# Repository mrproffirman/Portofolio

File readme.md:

**Projects that has been included are an already completed one and has been approved by all related party to be documented in this manner**

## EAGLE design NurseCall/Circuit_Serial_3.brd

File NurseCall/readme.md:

# Sistem Graphical User Interface untuk NurseCall Analog 

**Overview**<br />
Alat digunakan untuk membaca masukan dari sistem nursecall analog yang sudah ada. Pembacaan digunakan untuk menampilkan nomor kamar pada monitor dan melakukan panggilan pada audio. Secara hardware, sistem terdiri dari <br />
[NurseCall -> Hardware Interface -> SBC -> Monitor].

**Fitur Alat**
1. Membaca sinyal dari sistem NurseCall 0-24V sebanyak 36 Input biasa + 11 Emergency secara parallel
2. Isolasi sinyal input dari sistem utama 5V
3. Mengkonversi bacaan menjadi data digital yang dapat dibaca Single Board Computer.

*Sketsa Hubungan antara sistem monitor yang dibuat dengan NurseCall*

*Sirkuit Hardware Interface menggunakan Arduino Nano*

*GUI yang Dihasilkan*

*Hardware Interface*

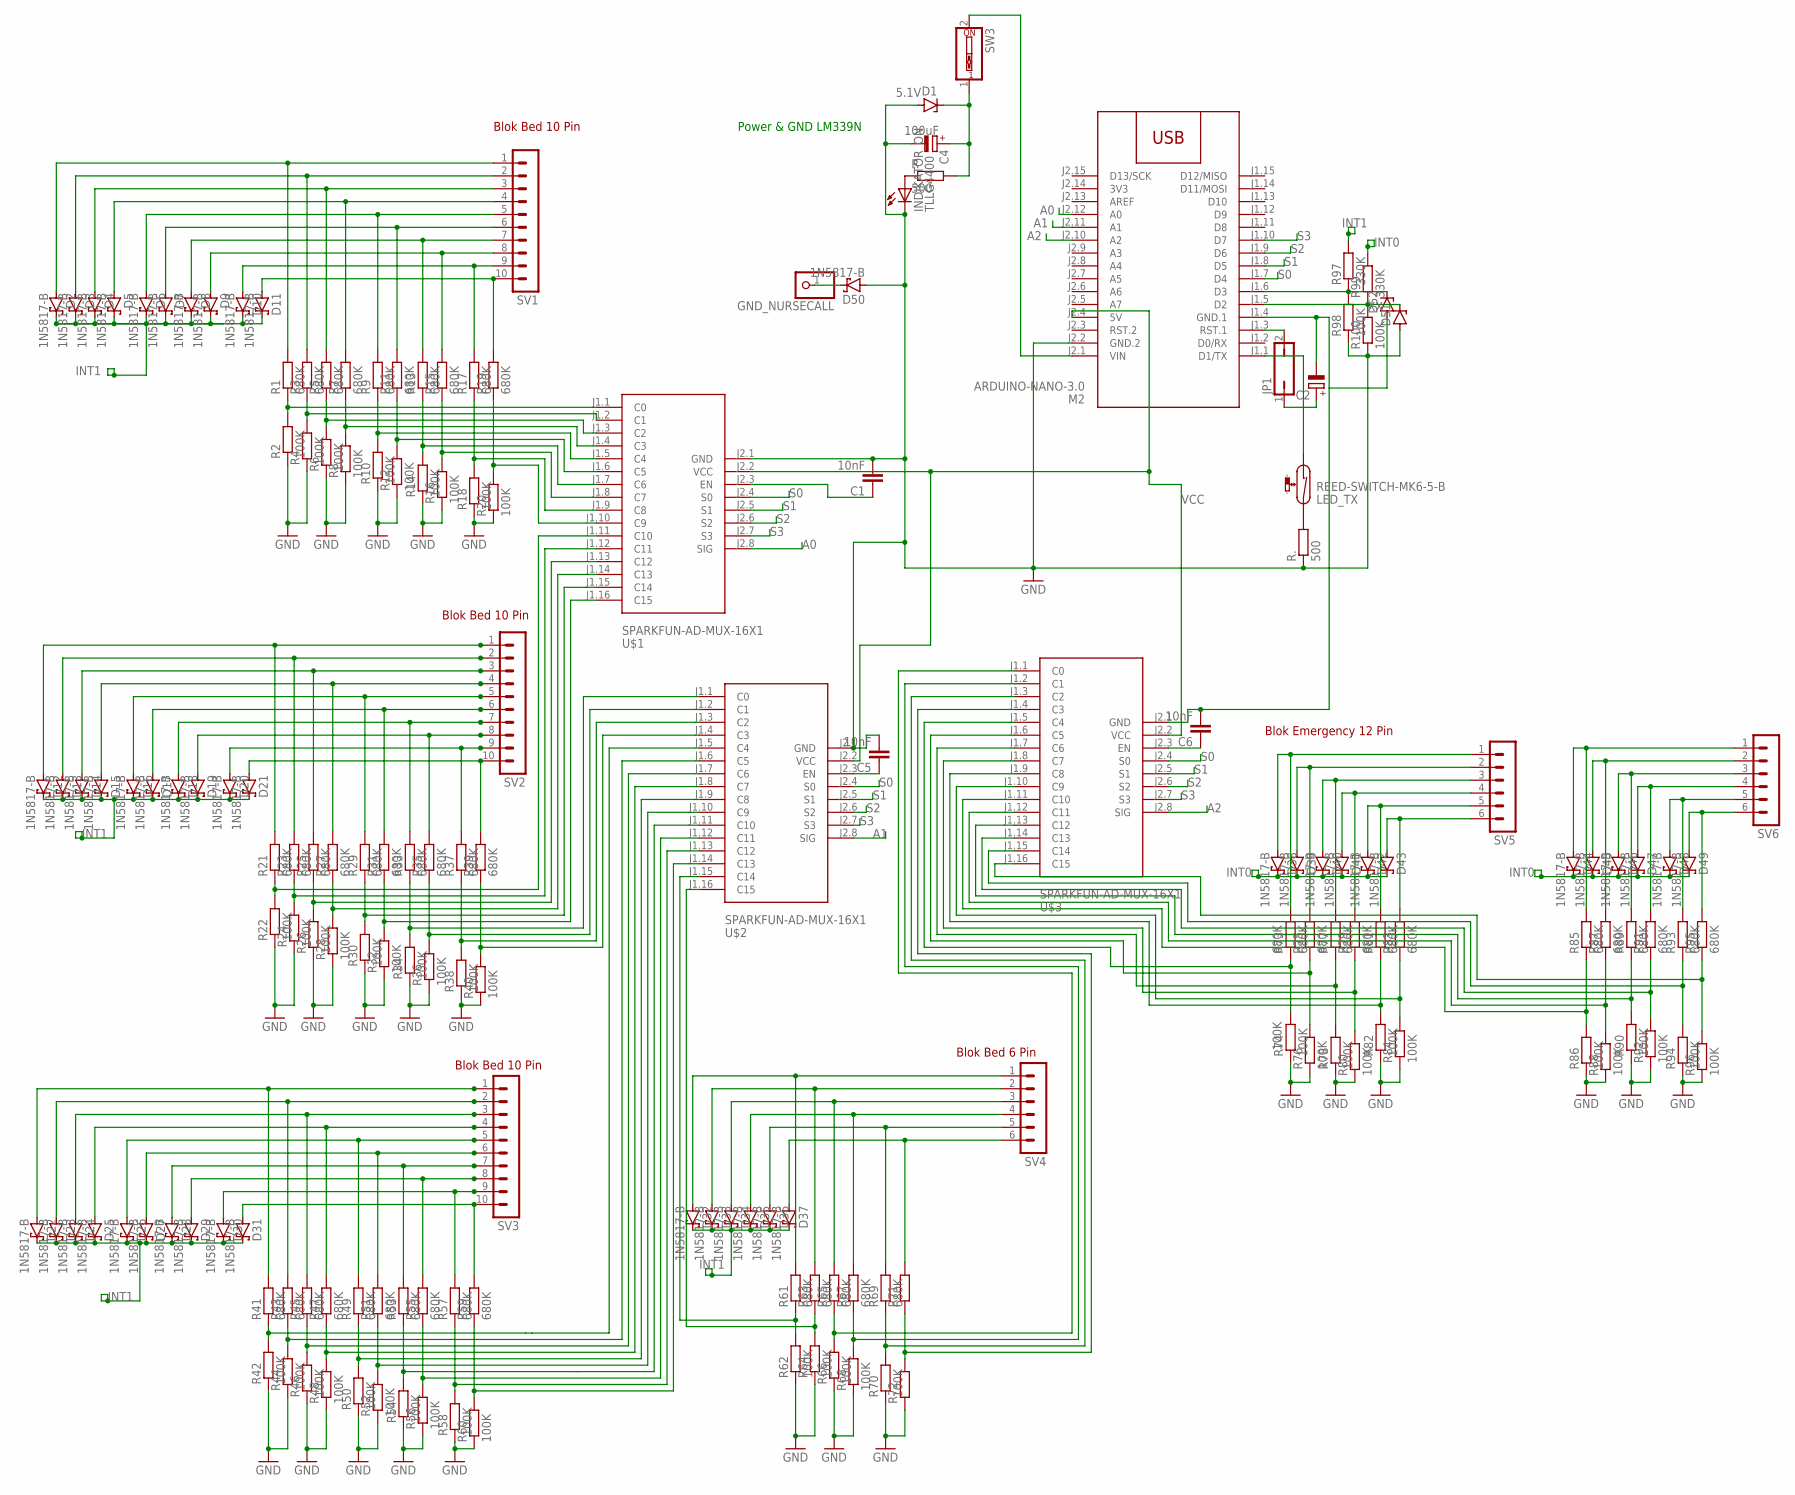
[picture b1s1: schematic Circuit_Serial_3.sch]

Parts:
C1, C5, C6: 10nF; C025-030X050
C2: CPOL-EUE3.5-8; E3,5-8
C4: 100uF; E3,5-10
D1: 5.1V; DO34Z7
D2, D3, D4, D5, D6, D7, D8, D9, D10, D11, D12, D13, D14, D15, D16, D17, D18, D19, D20, D21, D22, D23, D24, D25, D26, D27, D28, D29, D30, D31, D32, D33, D34, D35, D36, D37, D38, D39, D40, D41, D42, D43, D44, D45, D46, D47, D48, D49, D50: 1N5817-B; DO41-7.6
D51, D52: ZENER-DIODEDO34-7; DO34Z7
GND_NURSECALL: PINHD-1X1; 1X01
INDIKATOR_ON: TLLG4400; LED3MM
JP1: JP1Q; JP1
LED_TX: REED-SWITCH-MK6-5-B; MK6-5
M2: ARDUINO-NANO-3.0
R, R.: 500; 0204/7
R1, R3, R5, R7, R9, R11, R13, R15, R17, R19, R21, R23, R25, R27, R29, R31, R33, R35, R37, R39, R41, R43, R45, R47, R49, R51, R53, R55, R57, R59, R61, R63, R65, R67, R69, R71, R73, R75, R77, R79, R81, R83, R85, R87, R89, R91, R93, R95: 680K; 0204/7
R2, R4, R6, R8, R10, R12, R14, R16, R18, R20, R22, R24, R26, R28, R30, R32, R34, R36, R38, R40, R42, R44, R46, R48, R50, R52, R54, R56, R58, R60, R62, R64, R66, R68, R70, R72, R74, R76, R78, R80, R82, R84, R86, R88, R90, R92, R94, R96, R98, R100: 100K; 0204/7
R97, R99: 330K; 0204/7
SV1, SV2, SV3: MA10-1W
SV4, SV5, SV6: MA06-1
SW3: SW_DIP-1; EDG-01
U$1, U$2, U$3: SPARKFUN-AD-MUX-16X1

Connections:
3V3: M2.J2.14 (3V3)
A0: M2.J2.12 (A0), U$1.J2.8 (SIG)
A1: M2.J2.11 (A1), U$2.J2.8 (SIG)
A2: M2.J2.10 (A2), U$3.J2.8 (SIG)
GND: C1.2, C4.-, C5.2, D1.A, D50.A, D51.A, INDIKATOR_ON.K (C), M2.J2.2 (GND.2), R2.1, R4.1, R6.1, R8.1, R10.1, R12.1, R14.1, R16.1, R18.1, R20.1, R22.1, R24.1, R26.1, R28.1, R30.1, R32.1, R34.1, R36.1, R38.1, R40.1, R42.1, R44.1, R46.1, R48.1, R50.1, R52.1, R54.1, R56.1, R58.1, R60.1, R62.1, R64.1, R66.1, R68.1, R70.1, R72.1, R74.1, R76.1, R78.1, R80.1, R82.1, R84.1, R86.1, R88.1, R90.1, R92.1, R94.1, R96.1, R98.1, R100.1, R..1, U$1.J2.1 (GND), U$2.J2.1 (GND)
INT0: D38.C, D39.C, D40.C, D41.C, D42.C, D43.C, D44.C, D45.C, D46.C, D47.C, D48.C, D49.C, R99.2
INT1: D2.C, D3.C, D4.C, D5.C, D6.C, D7.C, D8.C, D9.C, D10.C, D11.C, D12.C, D13.C, D14.C, D15.C, D16.C, D17.C, D18.C, D19.C, D20.C, D21.C, D22.C, D23.C, D24.C, D25.C, D26.C, D27.C, D28.C, D29.C, D30.C, D31.C, D32.C, D33.C, D34.C, D35.C, D36.C, D37.C, R97.2
unnamed: D4.A, R5.2, SV1.3
unnamed: D2.A, R1.2, SV1.1
unnamed: D3.A, R3.2, SV1.2
unnamed: D11.A, R19.2, SV1.10
unnamed: D14.A, R25.2, SV2.3
unnamed: INDIKATOR_ON.A, R.1
unnamed: D12.A, R21.2, SV2.1
unnamed: R3.1, R4.2, U$1.J1.2 (C1)
unnamed: M2.J2.1 (VIN), SW3.2
unnamed: D15.A, R27.2, SV2.4
unnamed: D5.A, R7.2, SV1.4
unnamed: LED_TX.1, M2.J1.1 (D1/TX)
unnamed: R15.1, R16.2, U$1.J1.8 (C7)
unnamed: D18.A, R33.2, SV2.7
unnamed: D8.A, R13.2, SV1.7
unnamed: C5.1, U$2.J2.3 (EN)
unnamed: R17.1, R18.2, U$1.J1.9 (C8)
unnamed: D16.A, R29.2, SV2.5
unnamed: D17.A, R31.2, SV2.6
unnamed: R11.1, R12.2, U$1.J1.6 (C5)
unnamed: R19.1, R20.2, U$1.J1.10 (C9)
unnamed: R1.1, R2.2, U$1.J1.1 (C0)
unnamed: D6.A, R9.2, SV1.5
unnamed: R5.1, R6.2, U$1.J1.3 (C2)
unnamed: D19.A, R35.2, SV2.8
unnamed: D20.A, R37.2, SV2.9
unnamed: D7.A, R11.2, SV1.6
unnamed: D13.A, R23.2, SV2.2
unnamed: D21.A, R39.2, SV2.10
unnamed: D24.A, R45.2, SV3.3
unnamed: D22.A, R41.2, SV3.1
unnamed: R9.1, R10.2, U$1.J1.5 (C4)
unnamed: D25.A, R47.2, SV3.4
unnamed: R13.1, R14.2, U$1.J1.7 (C6)
unnamed: D28.A, R53.2, SV3.7
unnamed: R7.1, R8.2, U$1.J1.4 (C3)
unnamed: D9.A, R15.2, SV1.8
unnamed: D26.A, R49.2, SV3.5
unnamed: D10.A, R17.2, SV1.9
unnamed: D27.A, R51.2, SV3.6
unnamed: D29.A, R55.2, SV3.8
unnamed: D30.A, R57.2, SV3.9
unnamed: R31.1, R32.2, U$1.J1.16 (C15)
unnamed: R23.1, R24.2, U$1.J1.12 (C11)
unnamed: R35.1, R36.2, U$2.J1.2 (C1)
unnamed: R37.1, R38.2, U$2.J1.3 (C2)
unnamed: R39.1, R40.2, U$2.J1.4 (C3)
unnamed: R21.1, R22.2, U$1.J1.11 (C10)
unnamed: R25.1, R26.2, U$1.J1.13 (C12)
unnamed: R29.1, R30.2, U$1.J1.15 (C14)
unnamed: R33.1, R34.2, U$2.J1.1 (C0)
unnamed: R27.1, R28.2, U$1.J1.14 (C13)
unnamed: D23.A, R43.2, SV3.2
unnamed: D31.A, R59.2, SV3.10
unnamed: C6.1, U$3.J2.3 (EN)
unnamed: C1.1, U$1.J2.3 (EN)
unnamed: C2.-, C6.2, D52.A, M2.J1.4 (GND.1), U$3.J2.1 (GND)
unnamed: LED_TX.2, R..2
unnamed: D50.C, GND_NURSECALL.1
unnamed: C4.+, D1.C, R.2, SW3.1
unnamed: JP1.2, M2.J1.3 (RST.1)
unnamed: D52.C, M2.J1.6 (D3), R97.1, R98.2
unnamed: C2.+, JP1.1
unnamed: R63.1, R64.2, U$2.J1.16 (C15)
unnamed: R67.1, R68.2, U$3.J1.2 (C1)
unnamed: R51.1, R52.2, U$2.J1.10 (C9)
unnamed: R43.1, R44.2, U$2.J1.6 (C5)
unnamed: R55.1, R56.2, U$2.J1.12 (C11)
unnamed: R57.1, R58.2, U$2.J1.13 (C12)
unnamed: R59.1, R60.2, U$2.J1.14 (C13)
unnamed: R41.1, R42.2, U$2.J1.5 (C4)
unnamed: R45.1, R46.2, U$2.J1.7 (C6)
unnamed: R49.1, R50.2, U$2.J1.9 (C8)
unnamed: R53.1, R54.2, U$2.J1.11 (C10)
unnamed: R47.1, R48.2, U$2.J1.8 (C7)
unnamed: D46.A, R89.2, SV6.3
unnamed: D47.A, R91.2, SV6.4
unnamed: D34.A, R65.2, SV4.3
unnamed: D32.A, R61.2, SV4.1
unnamed: D35.A, R67.2, SV4.4
unnamed: D40.A, R77.2, SV5.3
unnamed: D36.A, R69.2, SV4.5
unnamed: D37.A, R71.2, SV4.6
unnamed: D41.A, R79.2, SV5.4
unnamed: D42.A, R81.2, SV5.5
unnamed: D33.A, R63.2, SV4.2
unnamed: R71.1, R72.2, U$3.J1.4 (C3)
unnamed: R73.1, R74.2, U$3.J1.5 (C4)
unnamed: R81.1, R82.2, U$3.J1.9 (C8)
unnamed: R85.1, R86.2, U$3.J1.11 (C10)
unnamed: R79.1, R80.2, U$3.J1.8 (C7)
unnamed: R61.1, R62.2, U$2.J1.15 (C14)
unnamed: R65.1, R66.2, U$3.J1.1 (C0)
unnamed: R69.1, R70.2, U$3.J1.3 (C2)
unnamed: R87.1, R88.2, U$3.J1.12 (C11)
unnamed: R89.1, R90.2, U$3.J1.13 (C12)
unnamed: D43.A, R83.2, SV5.6
unnamed: R75.1, R76.2, U$3.J1.6 (C5)
unnamed: R77.1, R78.2, U$3.J1.7 (C6)
unnamed: R91.1, R92.2, U$3.J1.14 (C13)
unnamed: D44.A, R85.2, SV6.1
unnamed: R83.1, R84.2, U$3.J1.10 (C9)
unnamed: R93.1, R94.2, U$3.J1.15 (C14)
unnamed: D45.A, R87.2, SV6.2
unnamed: D38.A, R73.2, SV5.1
unnamed: D39.A, R75.2, SV5.2
unnamed: D48.A, R93.2, SV6.5
unnamed: R95.1, R96.2, U$3.J1.16 (C15)
unnamed: D49.A, R95.2, SV6.6
S0: M2.J1.7 (D4), U$1.J2.4 (S0), U$2.J2.4 (S0), U$3.J2.4 (S0)
S1: M2.J1.8 (D5), U$1.J2.5 (S1), U$2.J2.5 (S1), U$3.J2.5 (S1)
S2: M2.J1.9 (D6), U$1.J2.6 (S2), U$2.J2.6 (S2), U$3.J2.6 (S2)
S3: M2.J1.10 (D7), U$1.J2.7 (S3), U$2.J2.7 (S3), U$3.J2.7 (S3)
VCC: M2.J2.4 (5V), U$1.J2.2 (VCC), U$2.J2.2 (VCC), U$3.J2.2 (VCC)
XX: D51.C, M2.J1.5 (D2), R99.1, R100.2

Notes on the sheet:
Power & GND LM339N
Blok Emergency 12 Pin
Blok Bed 6 Pin
Blok Bed 10 Pin

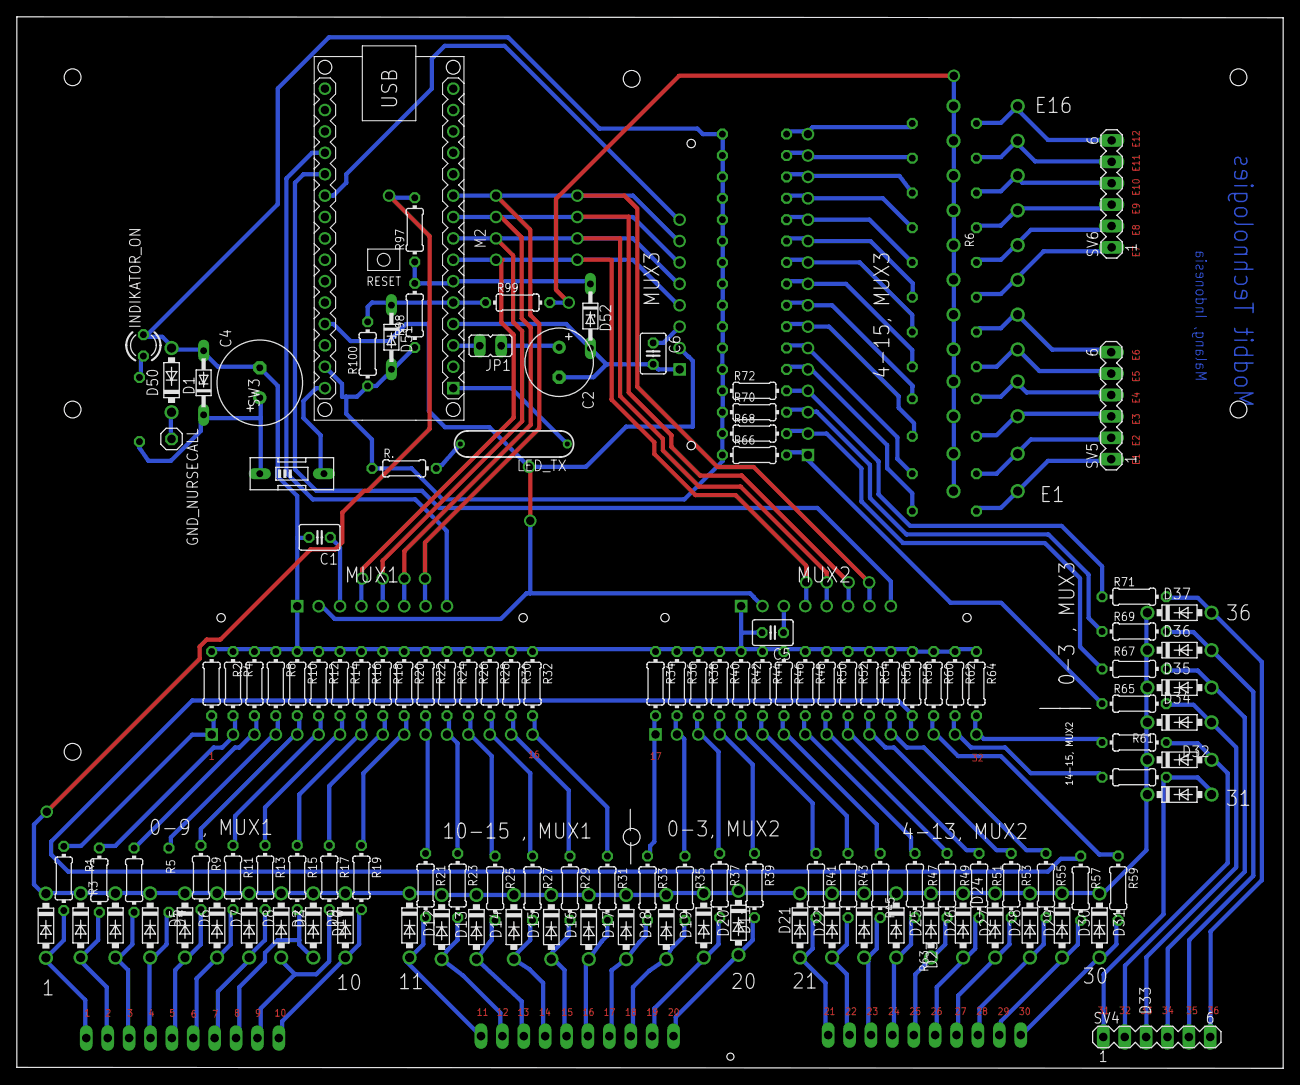
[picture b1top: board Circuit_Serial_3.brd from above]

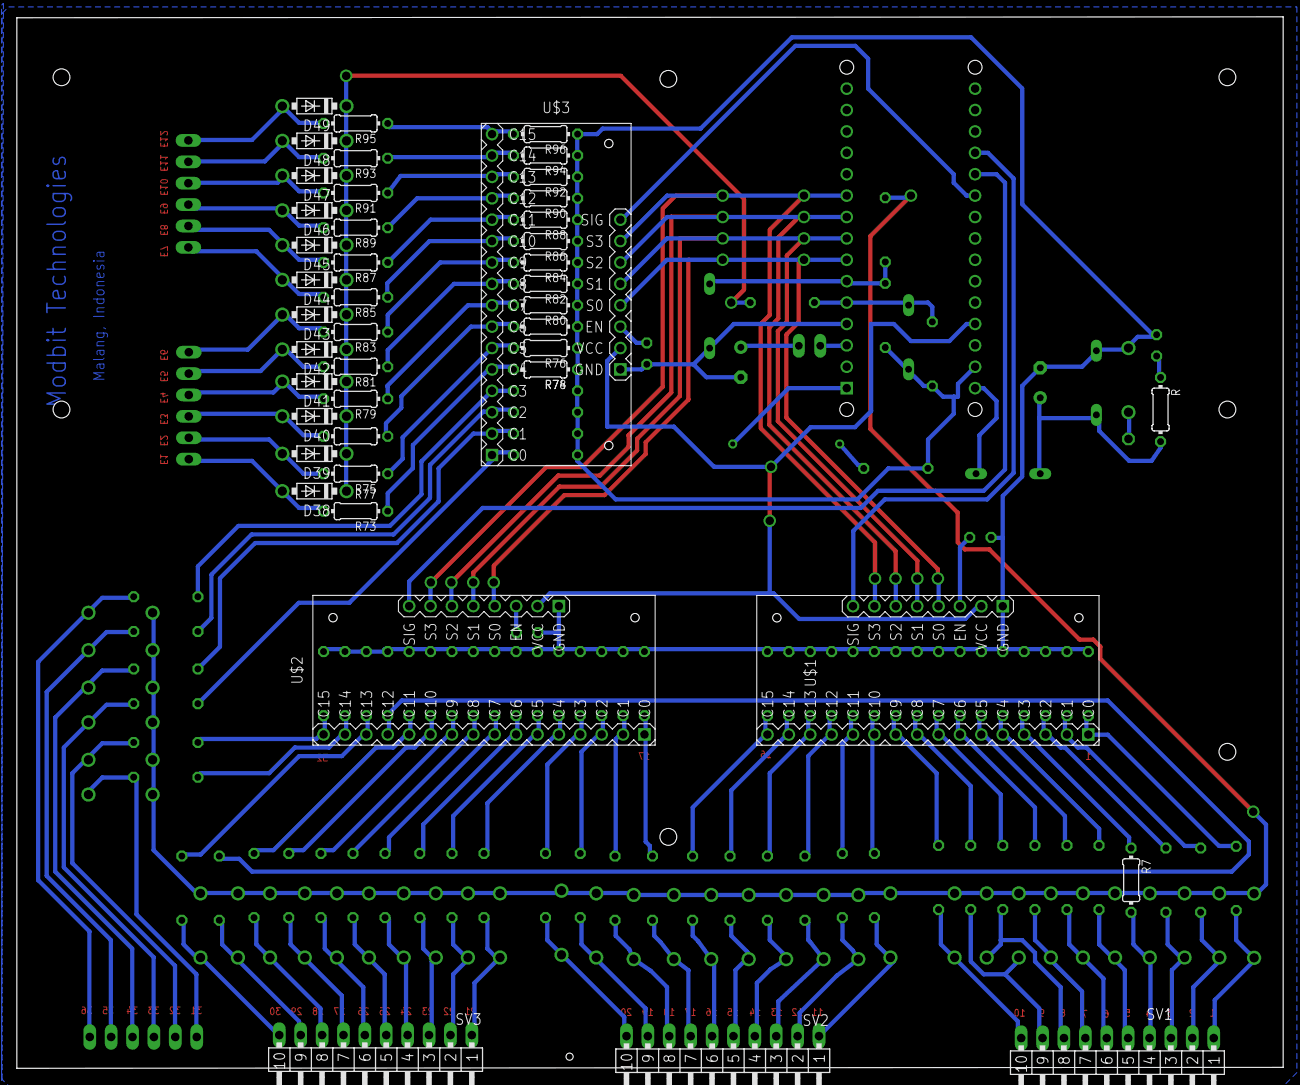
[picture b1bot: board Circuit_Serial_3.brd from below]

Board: 2 copper layers, 150.4 x 124.8 mm, 174 parts (44 on the bottom side), 121 nets.

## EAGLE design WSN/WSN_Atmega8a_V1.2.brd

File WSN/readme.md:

# Wireless Sensor Network Untuk Pertanian di Batu, Jawa Timur

**Fitur**
1. Dapat membaca parameter Suhu Udara, Kelembaban Udara, Kelembaban Tanah, dan Intensitas Cahaya
2. Bekerja secara wireless dengan menggunakan modul NRF24 sebagai metode komunikasi utama
3. Menggunakan Atmega8/168/328P sebagai mikrokontroller utama
4. Menggunakan catu daya baterai Li-ion 3.7V dan sel surya 6V

**Dimensi Alat**

**Keterangan Komponen**

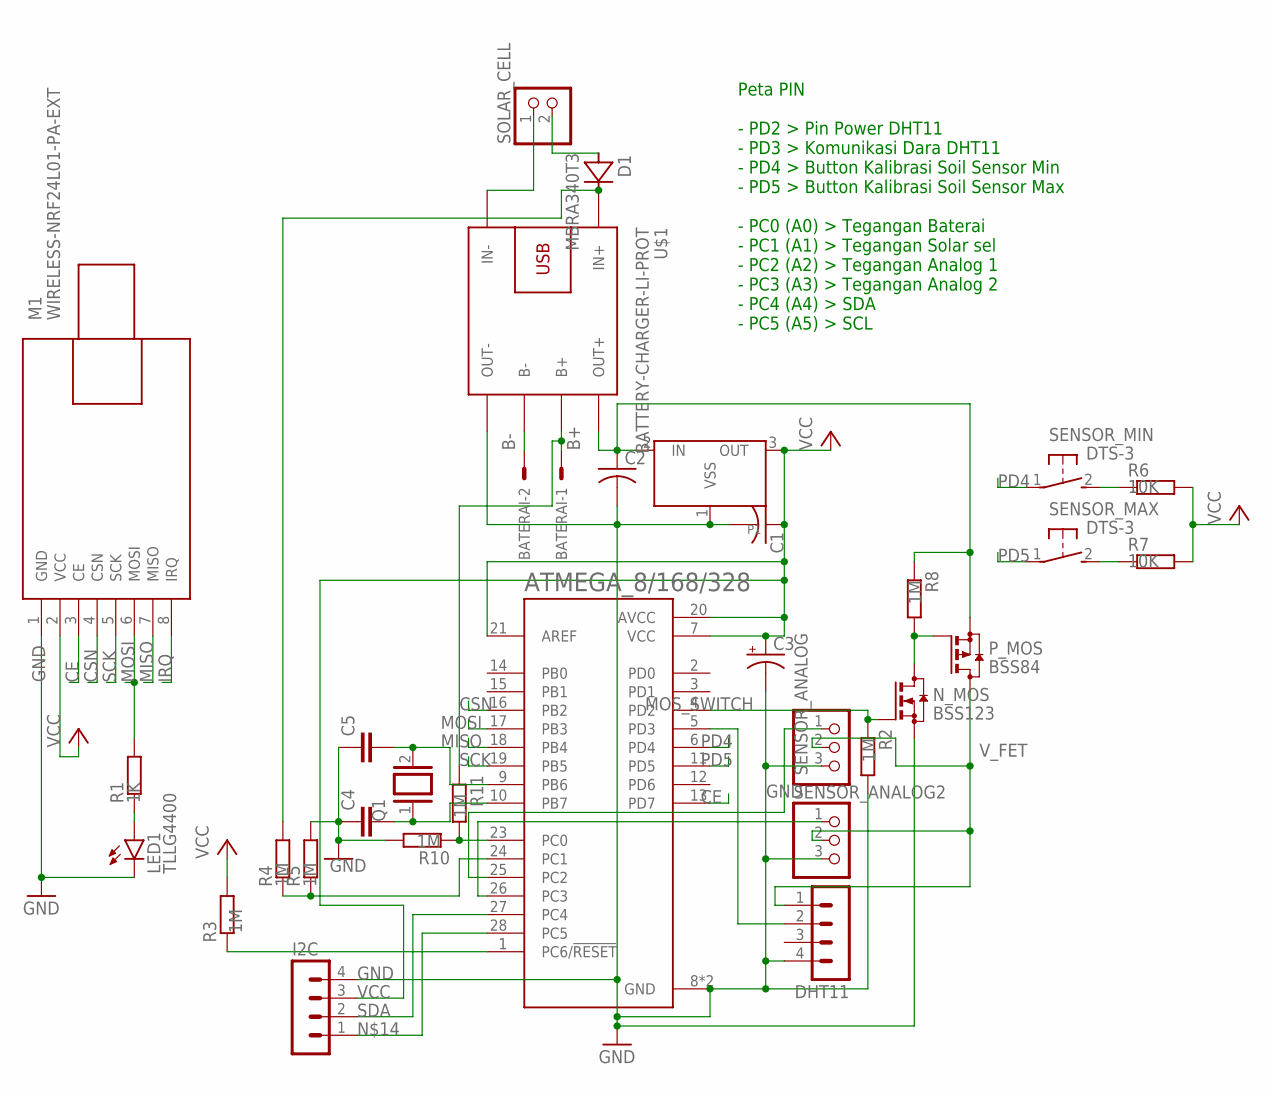
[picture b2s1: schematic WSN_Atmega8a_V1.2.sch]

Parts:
ATMEGA_8/168/328: ATMEGA328P-PU; DIP794W46P254L2967H457Q28B
BATERAI: 22-23-2021
C1, C2: C-USC0402; C0402
C3: CPOL-USE2.5-6; E2,5-6
C4, C5: C-EU025-024X044; C025-024X044
D1: MBRA340T3; SMA
DHT11: MA04-1
I2C: MA04-1
LED1: TLLG4400; LED3MM
M1: WIRELESS-NRF24L01-PA-EXT
N_MOS: BSS123; SOT23
P1: XC6206SOT-89; SOT-89
P_MOS: BSS84; SOT23
Q1: XTAL/S; QS
R1: 1K; R0805
R2, R3, R4, R5, R8, R10, R11: 1M; R0805
R6, R7: 10K; R0805
SENSOR_ANALOG, SENSOR_ANALOG2: PINHD-1X3/90; 1X03/90
SENSOR_MAX: DTS-3
SENSOR_MIN: DTS-3
SOLAR_CELL: PINHD-1X2; 1X02
U$1: BATTERY-CHARGER-LI-PROT

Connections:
B+: BATERAI.1, R11.1, U$1.B+
B-: BATERAI.2, U$1.B-
CE: ATMEGA_8/168/328.13 (PD7), M1.3 (CE)
CSN: ATMEGA_8/168/328.16 (PB2), M1.4 (CSN)
GND: ATMEGA_8/168/328.8 (GND), ATMEGA_8/168/328.22 (GND), C1.2, C2.2, C3.-, C4.1, C5.1, DHT11.4, I2C.4, LED1.K (C), M1.1 (GND), N_MOS.2 (S), P1.1 (VSS), R2.2, R5.2, R10.2, SENSOR_ANALOG.3, SENSOR_ANALOG2.3, U$1.OUT-
IRQ: M1.8 (IRQ)
MISO: ATMEGA_8/168/328.18 (PB4), M1.7 (MISO)
MOSI: ATMEGA_8/168/328.17 (PB3), M1.6 (MOSI), R1.2
MOS_SWITCH: ATMEGA_8/168/328.4 (PD2), N_MOS.1 (G), R2.1
unnamed: ATMEGA_8/168/328.1 (PC6/!RESET), R3.1
unnamed: C2.1, P1.2 (IN), P_MOS.2 (S), R8.1, U$1.OUT+
unnamed: LED1.A, R1.1
unnamed: R6.1, SENSOR_MIN.2
unnamed: ATMEGA_8/168/328.9 (PB6), C5.2, Q1.2
unnamed: ATMEGA_8/168/328.10 (PB7), C4.2, Q1.1
unnamed: R7.1, SENSOR_MAX.2
unnamed: N_MOS.3 (D), P_MOS.1 (G), R8.2
unnamed: ATMEGA_8/168/328.25 (PC2), SENSOR_ANALOG.1
unnamed: SOLAR_CELL.1, U$1.IN-
unnamed: ATMEGA_8/168/328.26 (PC3), SENSOR_ANALOG2.1
unnamed: D1.A, SOLAR_CELL.2
unnamed: ATMEGA_8/168/328.23 (PC0), R10.1, R11.2
unnamed: ATMEGA_8/168/328.28 (PC5), I2C.1
unnamed: ATMEGA_8/168/328.5 (PD3), DHT11.2
unnamed: ATMEGA_8/168/328.24 (PC1), R4.1, R5.1
unnamed: D1.C, R4.2, U$1.IN+
PD4: ATMEGA_8/168/328.6 (PD4), SENSOR_MIN.1
PD5: ATMEGA_8/168/328.11 (PD5), SENSOR_MAX.1
SCK: ATMEGA_8/168/328.19 (PB5), M1.5 (SCK)
SDA: ATMEGA_8/168/328.27 (PC4), I2C.2
VCC: ATMEGA_8/168/328.7 (VCC), ATMEGA_8/168/328.20 (AVCC), ATMEGA_8/168/328.21 (AREF), C1.1, C3.+, I2C.3, M1.2 (VCC), P1.3 (OUT), R3.2, R6.2, R7.2
V_FET: DHT11.1, P_MOS.3 (D), SENSOR_ANALOG.2, SENSOR_ANALOG2.2

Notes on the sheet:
Peta PIN - PD2 > Pin Power DHT11 - PD3 > Komunikasi Dara DHT11 - PD4 > Button Kalibrasi Soil Sensor Min - PD5 > Button Kalibrasi Soil Sensor Max - PC0 (A0) > Tegangan Baterai - PC1 (A1) > Tegangan Solar sel - PC2 (A2) > Tegangan Analog 1 - PC3 (A3) > Tegangan Analog 2 - PC4 (A4) > SDA - PC5 (A5) > 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

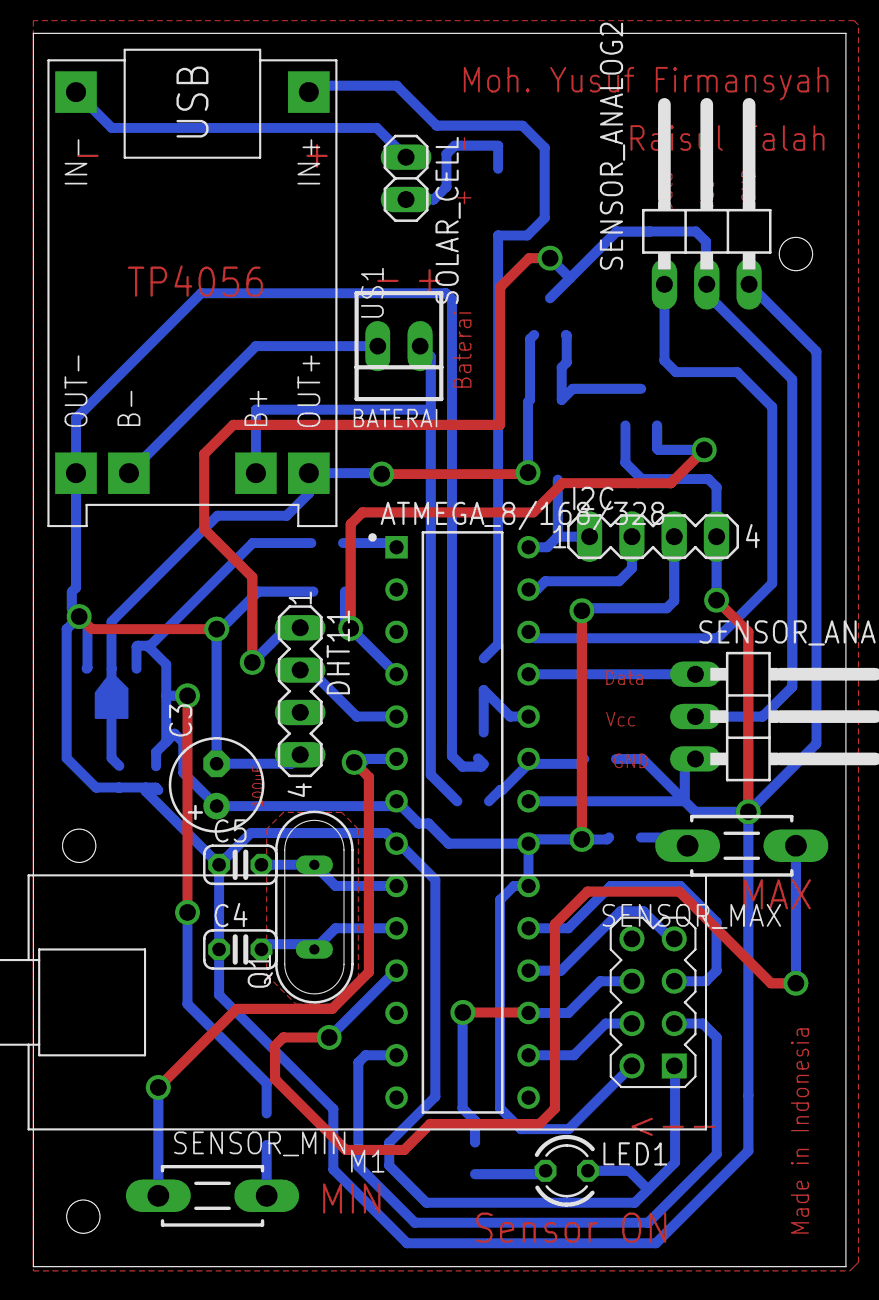
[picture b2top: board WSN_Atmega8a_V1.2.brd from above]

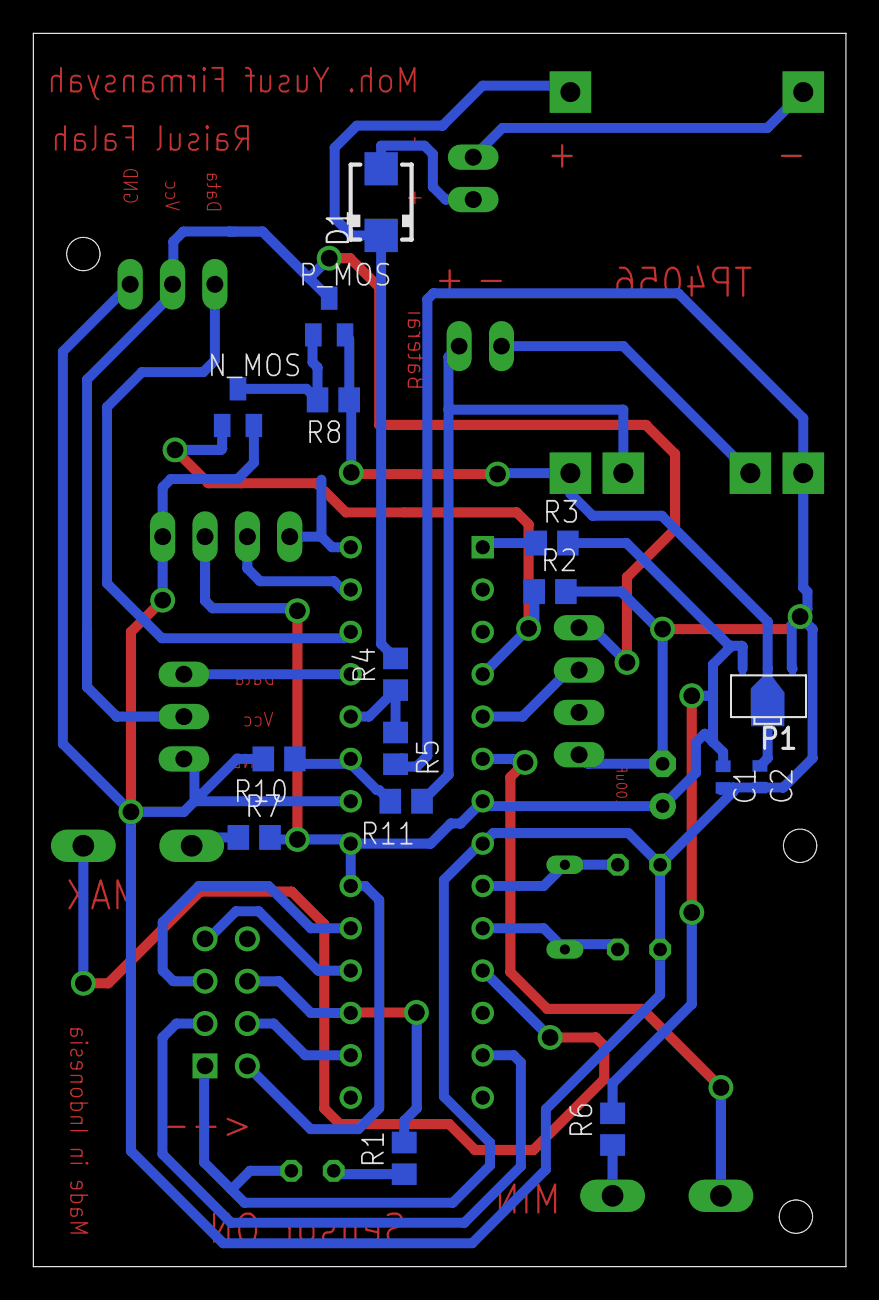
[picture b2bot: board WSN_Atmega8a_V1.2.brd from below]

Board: 2 copper layers, 48.8 x 74.0 mm, 32 parts (16 on the bottom side), 31 nets.

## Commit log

2021-09-14 Create sss
2021-11-22 Add files via upload
    This Is

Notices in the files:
parts and their libraries:
diy-modules: Released under the Creative Commons Attribution 4.0 International License: http://creativecommons.org/licenses/by/4.0
